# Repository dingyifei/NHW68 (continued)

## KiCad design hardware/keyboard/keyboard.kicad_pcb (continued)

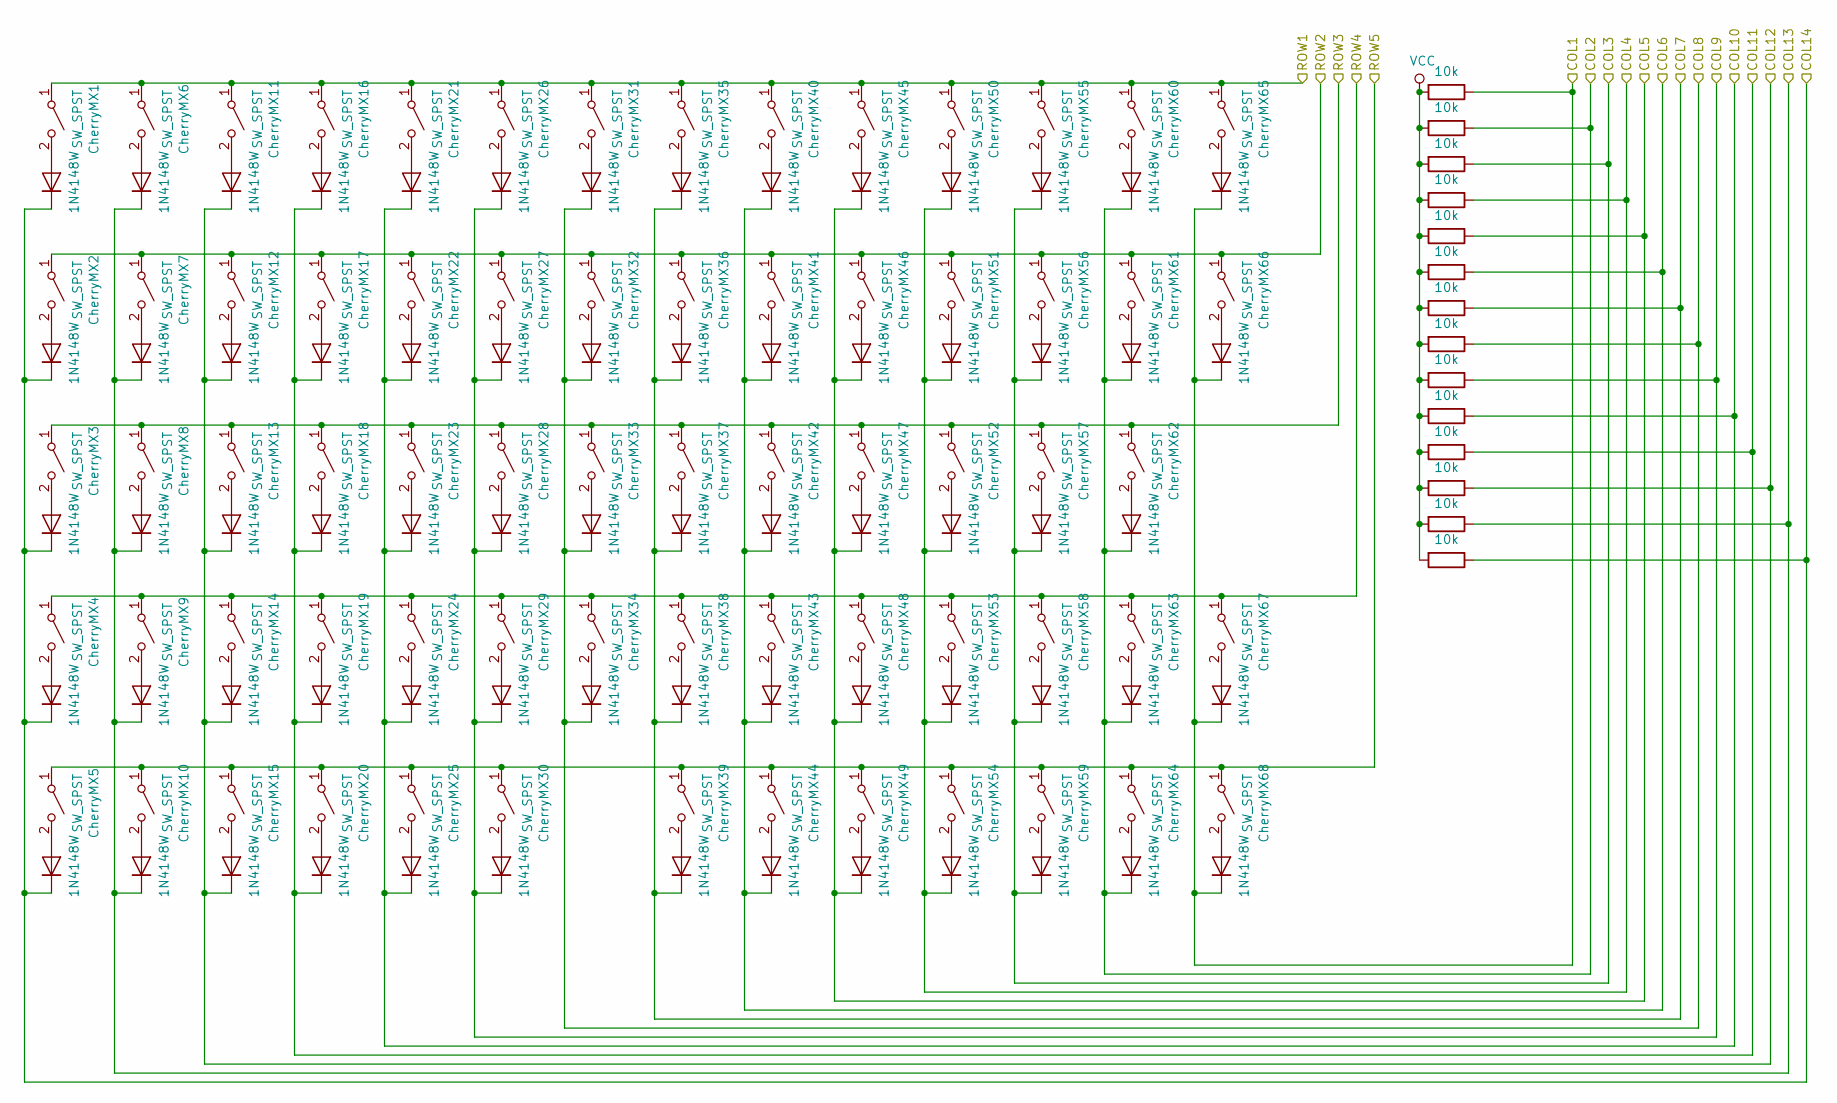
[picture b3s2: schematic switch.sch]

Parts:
CherryMX1, CherryMX2, CherryMX3, CherryMX4, CherryMX5, CherryMX6, CherryMX7, CherryMX8, CherryMX9, CherryMX10, CherryMX11, CherryMX12, CherryMX13, CherryMX14, CherryMX15, CherryMX16, CherryMX17, CherryMX18, CherryMX19, CherryMX20, CherryMX21, CherryMX22, CherryMX23, CherryMX24, CherryMX25, CherryMX26, CherryMX27, CherryMX28, CherryMX29, CherryMX30, CherryMX31, CherryMX32, CherryMX33, CherryMX34, CherryMX35, CherryMX36, CherryMX37, CherryMX38, CherryMX39, CherryMX40, CherryMX41, CherryMX42, CherryMX43, CherryMX44, CherryMX45, CherryMX46, CherryMX47, CherryMX48, CherryMX49, CherryMX50, CherryMX51, CherryMX52, CherryMX53, CherryMX54, CherryMX55, CherryMX56, CherryMX57, CherryMX58, CherryMX59, CherryMX60, CherryMX61, CherryMX62, CherryMX63, CherryMX64, CherryMX65, CherryMX66, CherryMX67, CherryMX68: SW_SPST; Kailh_socket_MX_optional_reversible
D1, D2, D3, D4, D5, D6, D7, D8, D9, D10, D11, D12, D13, D14, D15, D16, D17, D18, D19, D20, D21, D22, D23, D24, D25, D26, D27, D28, D29, D30, D31, D32, D33, D34, D35, D36, D37, D38, D39, D40, D41, D42, D43, D44, D45, D46, D47, D48, D49, D50, D51, D52, D53, D54, D55, D56, D57, D58, D59, D60, D61, D62, D63, D64, D65, D66, D67, D68: 1N4148W; D_SOD-123
R1, R2, R3, R4, R5, R6, R7, R8, R9, R10, R11, R12, R13, R14: 10k; R_0603_1608Metric_Pad1.05x0.95mm_HandSolder

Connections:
/switch/COL1: D65.1 (K), D66.1 (K), D67.1 (K), D68.1 (K), R1.1; also elsewhere on the board
/switch/COL2: D60.1 (K), D61.1 (K), D62.1 (K), D63.1 (K), D64.1 (K), R2.1; also elsewhere on the board
/switch/COL3: D55.1 (K), D56.1 (K), D57.1 (K), D58.1 (K), D59.1 (K), R3.1; also elsewhere on the board
/switch/COL4: D50.1 (K), D51.1 (K), D52.1 (K), D53.1 (K), D54.1 (K), R4.1; also elsewhere on the board
/switch/COL5: D45.1 (K), D46.1 (K), D47.1 (K), D48.1 (K), D49.1 (K), R5.1; also elsewhere on the board
/switch/COL6: D40.1 (K), D41.1 (K), D42.1 (K), D43.1 (K), D44.1 (K), R6.1; also elsewhere on the board
/switch/COL7: D35.1 (K), D36.1 (K), D37.1 (K), D38.1 (K), D39.1 (K), R7.1; also elsewhere on the board
/switch/COL8: D31.1 (K), D32.1 (K), D33.1 (K), D34.1 (K), R8.1; also elsewhere on the board
/switch/COL9: D26.1 (K), D27.1 (K), D28.1 (K), D29.1 (K), D30.1 (K), R9.1; also elsewhere on the board
/switch/COL10: D21.1 (K), D22.1 (K), D23.1 (K), D24.1 (K), D25.1 (K), R10.1; also elsewhere on the board
/switch/COL11: D16.1 (K), D17.1 (K), D18.1 (K), D19.1 (K), D20.1 (K), R11.1; also elsewhere on the board
/switch/COL12: D11.1 (K), D12.1 (K), D13.1 (K), D14.1 (K), D15.1 (K), R12.1; also elsewhere on the board
/switch/COL13: D6.1 (K), D7.1 (K), D8.1 (K), D9.1 (K), D10.1 (K), R13.1; also elsewhere on the board
/switch/COL14: D1.1 (K), D2.1 (K), D3.1 (K), D4.1 (K), D5.1 (K), R14.1; also elsewhere on the board
/switch/ROW1: CherryMX1.1 (A), CherryMX6.1 (A), CherryMX11.1 (A), CherryMX16.1 (A), CherryMX21.1 (A), CherryMX26.1 (A), CherryMX31.1 (A), CherryMX35.1 (A), CherryMX40.1 (A), CherryMX45.1 (A), CherryMX50.1 (A), CherryMX55.1 (A), CherryMX60.1 (A), CherryMX65.1 (A); also elsewhere on the board
/switch/ROW2: CherryMX2.1 (A), CherryMX7.1 (A), CherryMX12.1 (A), CherryMX17.1 (A), CherryMX22.1 (A), CherryMX27.1 (A), CherryMX32.1 (A), CherryMX36.1 (A), CherryMX41.1 (A), CherryMX46.1 (A), CherryMX51.1 (A), CherryMX56.1 (A), CherryMX61.1 (A), CherryMX66.1 (A); also elsewhere on the board
/switch/ROW3: CherryMX3.1 (A), CherryMX8.1 (A), CherryMX13.1 (A), CherryMX18.1 (A), CherryMX23.1 (A), CherryMX28.1 (A), CherryMX33.1 (A), CherryMX37.1 (A), CherryMX42.1 (A), CherryMX47.1 (A), CherryMX52.1 (A), CherryMX57.1 (A), CherryMX62.1 (A); also elsewhere on the board
/switch/ROW4: CherryMX4.1 (A), CherryMX9.1 (A), CherryMX14.1 (A), CherryMX19.1 (A), CherryMX24.1 (A), CherryMX29.1 (A), CherryMX34.1 (A), CherryMX38.1 (A), CherryMX43.1 (A), CherryMX48.1 (A), CherryMX53.1 (A), CherryMX58.1 (A), CherryMX63.1 (A), CherryMX67.1 (A); also elsewhere on the board
/switch/ROW5: CherryMX5.1 (A), CherryMX10.1 (A), CherryMX15.1 (A), CherryMX20.1 (A), CherryMX25.1 (A), CherryMX30.1 (A), CherryMX39.1 (A), CherryMX44.1 (A), CherryMX49.1 (A), CherryMX54.1 (A), CherryMX59.1 (A), CherryMX64.1 (A), CherryMX68.1 (A); also elsewhere on the board
unnamed: CherryMX1.2 (B), D1.2 (A)
unnamed: CherryMX2.2 (B), D2.2 (A)
unnamed: CherryMX3.2 (B), D3.2 (A)
unnamed: CherryMX4.2 (B), D4.2 (A)
unnamed: CherryMX5.2 (B), D5.2 (A)
unnamed: CherryMX6.2 (B), D6.2 (A)
unnamed: CherryMX7.2 (B), D7.2 (A)
unnamed: CherryMX8.2 (B), D8.2 (A)
unnamed: CherryMX9.2 (B), D9.2 (A)
unnamed: CherryMX10.2 (B), D10.2 (A)
unnamed: CherryMX11.2 (B), D11.2 (A)
unnamed: CherryMX12.2 (B), D12.2 (A)
unnamed: CherryMX13.2 (B), D13.2 (A)
unnamed: CherryMX14.2 (B), D14.2 (A)
unnamed: CherryMX15.2 (B), D15.2 (A)
unnamed: CherryMX16.2 (B), D16.2 (A)
unnamed: CherryMX17.2 (B), D17.2 (A)
unnamed: CherryMX18.2 (B), D18.2 (A)
unnamed: CherryMX19.2 (B), D19.2 (A)
unnamed: CherryMX20.2 (B), D20.2 (A)
unnamed: CherryMX21.2 (B), D21.2 (A)
unnamed: CherryMX22.2 (B), D22.2 (A)
unnamed: CherryMX23.2 (B), D23.2 (A)
unnamed: CherryMX24.2 (B), D24.2 (A)
unnamed: CherryMX25.2 (B), D25.2 (A)
unnamed: CherryMX26.2 (B), D26.2 (A)
unnamed: CherryMX27.2 (B), D27.2 (A)
unnamed: CherryMX28.2 (B), D28.2 (A)
unnamed: CherryMX29.2 (B), D29.2 (A)
unnamed: CherryMX30.2 (B), D30.2 (A)
unnamed: CherryMX31.2 (B), D31.2 (A)
unnamed: CherryMX32.2 (B), D32.2 (A)
unnamed: CherryMX33.2 (B), D33.2 (A)
unnamed: CherryMX34.2 (B), D34.2 (A)
unnamed: CherryMX35.2 (B), D35.2 (A)
unnamed: CherryMX36.2 (B), D36.2 (A)
unnamed: CherryMX37.2 (B), D37.2 (A)
unnamed: CherryMX38.2 (B), D38.2 (A)
unnamed: CherryMX39.2 (B), D39.2 (A)
unnamed: CherryMX40.2 (B), D40.2 (A)
unnamed: CherryMX41.2 (B), D41.2 (A)
unnamed: CherryMX42.2 (B), D42.2 (A)
unnamed: CherryMX43.2 (B), D43.2 (A)
unnamed: CherryMX44.2 (B), D44.2 (A)
unnamed: CherryMX45.2 (B), D45.2 (A)
unnamed: CherryMX46.2 (B), D46.2 (A)
unnamed: CherryMX47.2 (B), D47.2 (A)
unnamed: CherryMX48.2 (B), D48.2 (A)
unnamed: CherryMX49.2 (B), D49.2 (A)
unnamed: CherryMX50.2 (B), D50.2 (A)
unnamed: CherryMX51.2 (B), D51.2 (A)
unnamed: CherryMX52.2 (B), D52.2 (A)
unnamed: CherryMX53.2 (B), D53.2 (A)
unnamed: CherryMX54.2 (B), D54.2 (A)
unnamed: CherryMX55.2 (B), D55.2 (A)
unnamed: CherryMX56.2 (B), D56.2 (A)
unnamed: CherryMX57.2 (B), D57.2 (A)
unnamed: CherryMX58.2 (B), D58.2 (A)
unnamed: CherryMX59.2 (B), D59.2 (A)
unnamed: CherryMX60.2 (B), D60.2 (A)
unnamed: CherryMX61.2 (B), D61.2 (A)
unnamed: CherryMX62.2 (B), D62.2 (A)
unnamed: CherryMX63.2 (B), D63.2 (A)
unnamed: CherryMX64.2 (B), D64.2 (A)
unnamed: CherryMX65.2 (B), D65.2 (A)
unnamed: CherryMX66.2 (B), D66.2 (A)
unnamed: CherryMX67.2 (B), D67.2 (A)
unnamed: CherryMX68.2 (B), D68.2 (A)
VCC: R1.2, R2.2, R3.2, R4.2, R5.2, R6.2, R7.2, R8.2, R9.2, R10.2, R11.2, R12.2, R13.2, R14.2; also elsewhere on the board

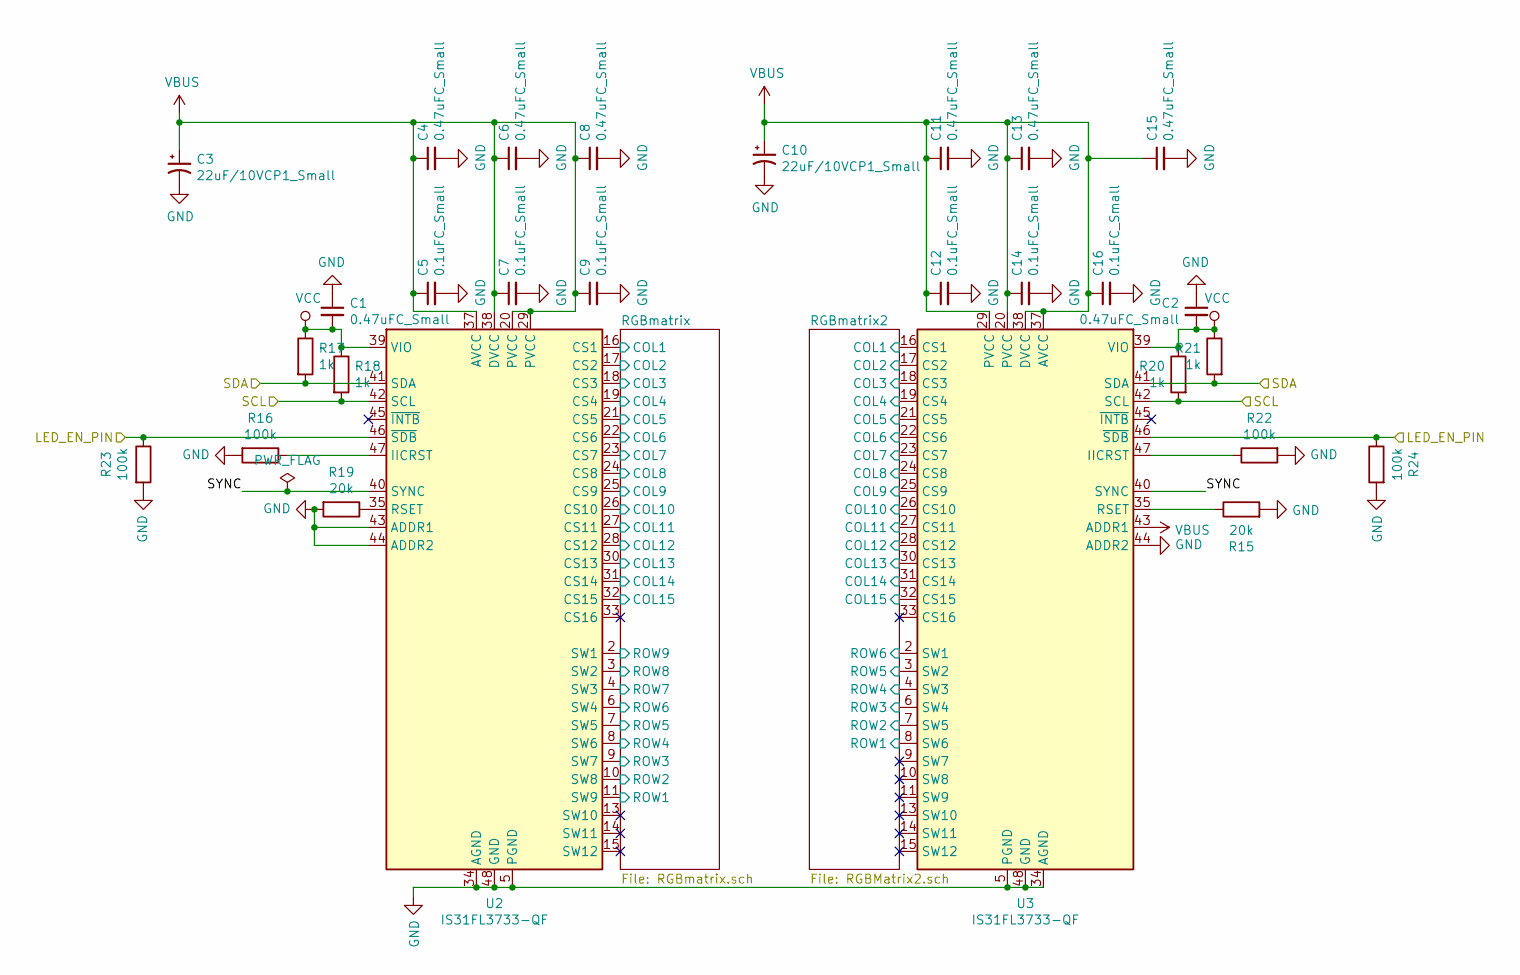
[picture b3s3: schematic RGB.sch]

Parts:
C1, C2, C4, C6, C8, C11, C13, C15: 0.47uFC_Small; C_0603_1608Metric_Pad1.05x0.95mm_HandSolder
C3, C10: 22uF/10VCP1_Small; CP_EIA-3528-12_Kemet-T_Pad1.50x2.35mm_HandSolder
C5, C7, C9, C12, C14, C16: 0.1uFC_Small; C_0603_1608Metric_Pad1.05x0.95mm_HandSolder
R15, R19: 20k; R_0603_1608Metric_Pad1.05x0.95mm_HandSolder
R16, R22, R23, R24: 100k; R_0603_1608Metric_Pad1.05x0.95mm_HandSolder
R17, R18, R20, R21: 1k; R_0603_1608Metric_Pad1.05x0.95mm_HandSolder
U2, U3: IS31FL3733-QF; QFN-48-1EP_6x6mm_P0.4mm_EP4.2x4.2mm_ThermalVias

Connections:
/RGB/LED_EN_PIN: R23.1, R24.1, U2.46 (~SDB), U3.46 (~SDB); also elsewhere on the board
/RGB/RGBmatrix2/COL1: U3.16 (CS1); also elsewhere on the board
/RGB/RGBmatrix2/COL2: U3.17 (CS2); also elsewhere on the board
/RGB/RGBmatrix2/COL3: U3.18 (CS3); also elsewhere on the board
/RGB/RGBmatrix2/COL4: U3.19 (CS4); also elsewhere on the board
/RGB/RGBmatrix2/COL5: U3.21 (CS5); also elsewhere on the board
/RGB/RGBmatrix2/COL6: U3.22 (CS6); also elsewhere on the board
/RGB/RGBmatrix2/COL7: U3.23 (CS7); also elsewhere on the board
/RGB/RGBmatrix2/COL8: U3.24 (CS8); also elsewhere on the board
/RGB/RGBmatrix2/COL9: U3.25 (CS9); also elsewhere on the board
/RGB/RGBmatrix2/COL10: U3.26 (CS10); also elsewhere on the board
/RGB/RGBmatrix2/COL11: U3.27 (CS11); also elsewhere on the board
/RGB/RGBmatrix2/COL12: U3.28 (CS12); also elsewhere on the board
/RGB/RGBmatrix2/COL13: U3.30 (CS13); also elsewhere on the board
/RGB/RGBmatrix2/COL14: U3.31 (CS14); also elsewhere on the board
/RGB/RGBmatrix2/COL15: U3.32 (CS15); also elsewhere on the board
/RGB/RGBmatrix2/ROW1: U3.8 (SW6); also elsewhere on the board
/RGB/RGBmatrix2/ROW2: U3.7 (SW5); also elsewhere on the board
/RGB/RGBmatrix2/ROW3: U3.6 (SW4); also elsewhere on the board
/RGB/RGBmatrix2/ROW4: U3.4 (SW3); also elsewhere on the board
/RGB/RGBmatrix2/ROW5: U3.3 (SW2); also elsewhere on the board
/RGB/RGBmatrix2/ROW6: U3.2 (SW1); also elsewhere on the board
/RGB/RGBmatrix/COL1: U2.16 (CS1); also elsewhere on the board
/RGB/RGBmatrix/COL2: U2.17 (CS2); also elsewhere on the board
/RGB/RGBmatrix/COL3: U2.18 (CS3); also elsewhere on the board
/RGB/RGBmatrix/COL4: U2.19 (CS4); also elsewhere on the board
/RGB/RGBmatrix/COL5: U2.21 (CS5); also elsewhere on the board
/RGB/RGBmatrix/COL6: U2.22 (CS6); also elsewhere on the board
/RGB/RGBmatrix/COL7: U2.23 (CS7); also elsewhere on the board
/RGB/RGBmatrix/COL8: U2.24 (CS8); also elsewhere on the board
/RGB/RGBmatrix/COL9: U2.25 (CS9); also elsewhere on the board
/RGB/RGBmatrix/COL10: U2.26 (CS10); also elsewhere on the board
/RGB/RGBmatrix/COL11: U2.27 (CS11); also elsewhere on the board
/RGB/RGBmatrix/COL12: U2.28 (CS12); also elsewhere on the board
/RGB/RGBmatrix/COL13: U2.30 (CS13); also elsewhere on the board
/RGB/RGBmatrix/COL14: U2.31 (CS14); also elsewhere on the board
/RGB/RGBmatrix/COL15: U2.32 (CS15); also elsewhere on the board
/RGB/RGBmatrix/ROW1: U2.11 (SW9); also elsewhere on the board
/RGB/RGBmatrix/ROW2: U2.10 (SW8); also elsewhere on the board
/RGB/RGBmatrix/ROW3: U2.9 (SW7); also elsewhere on the board
/RGB/RGBmatrix/ROW4: U2.8 (SW6); also elsewhere on the board
/RGB/RGBmatrix/ROW5: U2.7 (SW5); also elsewhere on the board
/RGB/RGBmatrix/ROW6: U2.6 (SW4); also elsewhere on the board
/RGB/RGBmatrix/ROW7: U2.4 (SW3); also elsewhere on the board
/RGB/RGBmatrix/ROW8: U2.3 (SW2); also elsewhere on the board
/RGB/RGBmatrix/ROW9: U2.2 (SW1); also elsewhere on the board
/RGB/SCL: R18.2, R20.2, U2.42 (SCL), U3.42 (SCL); also elsewhere on the board
/RGB/SDA: R17.2, R21.2, U2.41 (SDA), U3.41 (SDA); also elsewhere on the board
/RGB/SYNC: U2.40 (SYNC), U3.40 (SYNC)
GND: C1.1, C2.1, C3.2, C4.2, C5.2, C6.2, C7.2, C8.2, C9.2, C10.2, C11.2, C12.2, C13.2, C14.2, C15.2, C16.2, R15.2, R16.2, R19.2, R22.2, R23.2, R24.2, U2.5 (PGND), U2.12 (PGND), U2.34 (AGND), U2.43 (ADDR1), U2.44 (ADDR2), U2.48 (GND), U2.49 (GND), U3.5 (PGND), U3.12 (PGND), U3.34 (AGND), U3.44 (ADDR2), U3.48 (GND), U3.49 (GND); also elsewhere on the board
unnamed: R15.1, U3.35 (RSET)
unnamed: R16.1, U2.47 (IICRST)
unnamed: R19.1, U2.35 (RSET)
unnamed: R22.1, U3.47 (IICRST)
VBUS: C3.1, C4.1, C5.1, C6.1, C7.1, C8.1, C9.1, C10.1, C11.1, C12.1, C13.1, C14.1, C15.1, C16.1, U2.20 (PVCC), U2.29 (PVCC), U2.37 (AVCC), U2.38 (DVCC), U3.20 (PVCC), U3.29 (PVCC), U3.37 (AVCC), U3.38 (DVCC), U3.43 (ADDR1); also elsewhere on the board
VCC: C1.2, C2.2, R17.1, R18.1, R20.1, R21.1, U2.39 (VIO), U3.39 (VIO); also elsewhere on the board

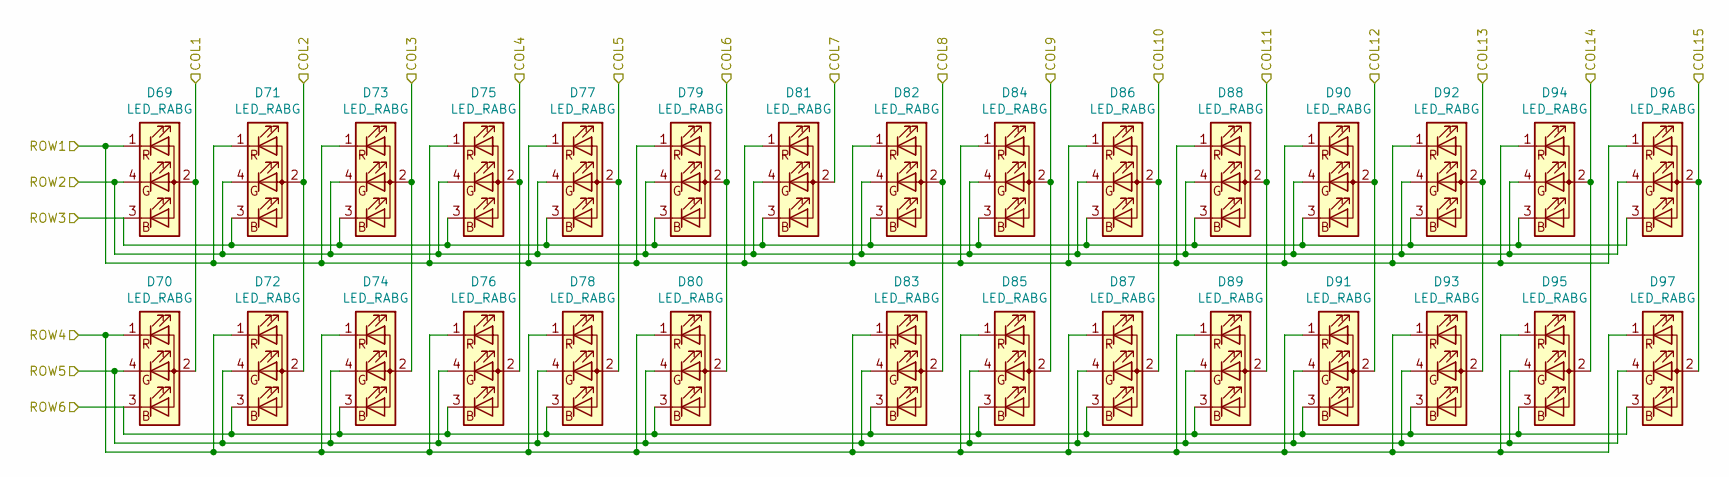
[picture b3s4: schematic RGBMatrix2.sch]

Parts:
D69, D70, D71, D72, D73, D74, D75, D76, D77, D78, D79, D80, D81, D82, D83, D84, D85, D86, D87, D88, D89, D90, D91, D92, D93, D94, D95, D96, D97: LED_RABG

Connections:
/RGB/RGBmatrix2/COL1: D69.2 (A), D70.2 (A); also elsewhere on the board
/RGB/RGBmatrix2/COL2: D71.2 (A), D72.2 (A); also elsewhere on the board
/RGB/RGBmatrix2/COL3: D73.2 (A), D74.2 (A); also elsewhere on the board
/RGB/RGBmatrix2/COL4: D75.2 (A), D76.2 (A); also elsewhere on the board
/RGB/RGBmatrix2/COL5: D77.2 (A), D78.2 (A); also elsewhere on the board
/RGB/RGBmatrix2/COL6: D79.2 (A), D80.2 (A); also elsewhere on the board
/RGB/RGBmatrix2/COL7: D81.2 (A); also elsewhere on the board
/RGB/RGBmatrix2/COL8: D82.2 (A), D83.2 (A); also elsewhere on the board
/RGB/RGBmatrix2/COL9: D84.2 (A), D85.2 (A); also elsewhere on the board
/RGB/RGBmatrix2/COL10: D86.2 (A), D87.2 (A); also elsewhere on the board
/RGB/RGBmatrix2/COL11: D88.2 (A), D89.2 (A); also elsewhere on the board
/RGB/RGBmatrix2/COL12: D90.2 (A), D91.2 (A); also elsewhere on the board
/RGB/RGBmatrix2/COL13: D92.2 (A), D93.2 (A); also elsewhere on the board
/RGB/RGBmatrix2/COL14: D94.2 (A), D95.2 (A); also elsewhere on the board
/RGB/RGBmatrix2/COL15: D96.2 (A), D97.2 (A); also elsewhere on the board
/RGB/RGBmatrix2/ROW1: D69.1 (RK), D71.1 (RK), D73.1 (RK), D75.1 (RK), D77.1 (RK), D79.1 (RK), D81.1 (RK), D82.1 (RK), D84.1 (RK), D86.1 (RK), D88.1 (RK), D90.1 (RK), D92.1 (RK), D94.1 (RK), D96.1 (RK); also elsewhere on the board
/RGB/RGBmatrix2/ROW2: D69.4 (GK), D71.4 (GK), D73.4 (GK), D75.4 (GK), D77.4 (GK), D79.4 (GK), D81.4 (GK), D82.4 (GK), D84.4 (GK), D86.4 (GK), D88.4 (GK), D90.4 (GK), D92.4 (GK), D94.4 (GK), D96.4 (GK); also elsewhere on the board
/RGB/RGBmatrix2/ROW3: D69.3 (BK), D71.3 (BK), D73.3 (BK), D75.3 (BK), D77.3 (BK), D79.3 (BK), D81.3 (BK), D82.3 (BK), D84.3 (BK), D86.3 (BK), D88.3 (BK), D90.3 (BK), D92.3 (BK), D94.3 (BK), D96.3 (BK); also elsewhere on the board
/RGB/RGBmatrix2/ROW4: D70.1 (RK), D72.1 (RK), D74.1 (RK), D76.1 (RK), D78.1 (RK), D80.1 (RK), D83.1 (RK), D85.1 (RK), D87.1 (RK), D89.1 (RK), D91.1 (RK), D93.1 (RK), D95.1 (RK), D97.1 (RK); also elsewhere on the board
/RGB/RGBmatrix2/ROW5: D70.4 (GK), D72.4 (GK), D74.4 (GK), D76.4 (GK), D78.4 (GK), D80.4 (GK), D83.4 (GK), D85.4 (GK), D87.4 (GK), D89.4 (GK), D91.4 (GK), D93.4 (GK), D95.4 (GK), D97.4 (GK); also elsewhere on the board
/RGB/RGBmatrix2/ROW6: D70.3 (BK), D72.3 (BK), D74.3 (BK), D76.3 (BK), D78.3 (BK), D80.3 (BK), D83.3 (BK), D85.3 (BK), D87.3 (BK), D89.3 (BK), D91.3 (BK), D93.3 (BK), D95.3 (BK), D97.3 (BK); also elsewhere on the board

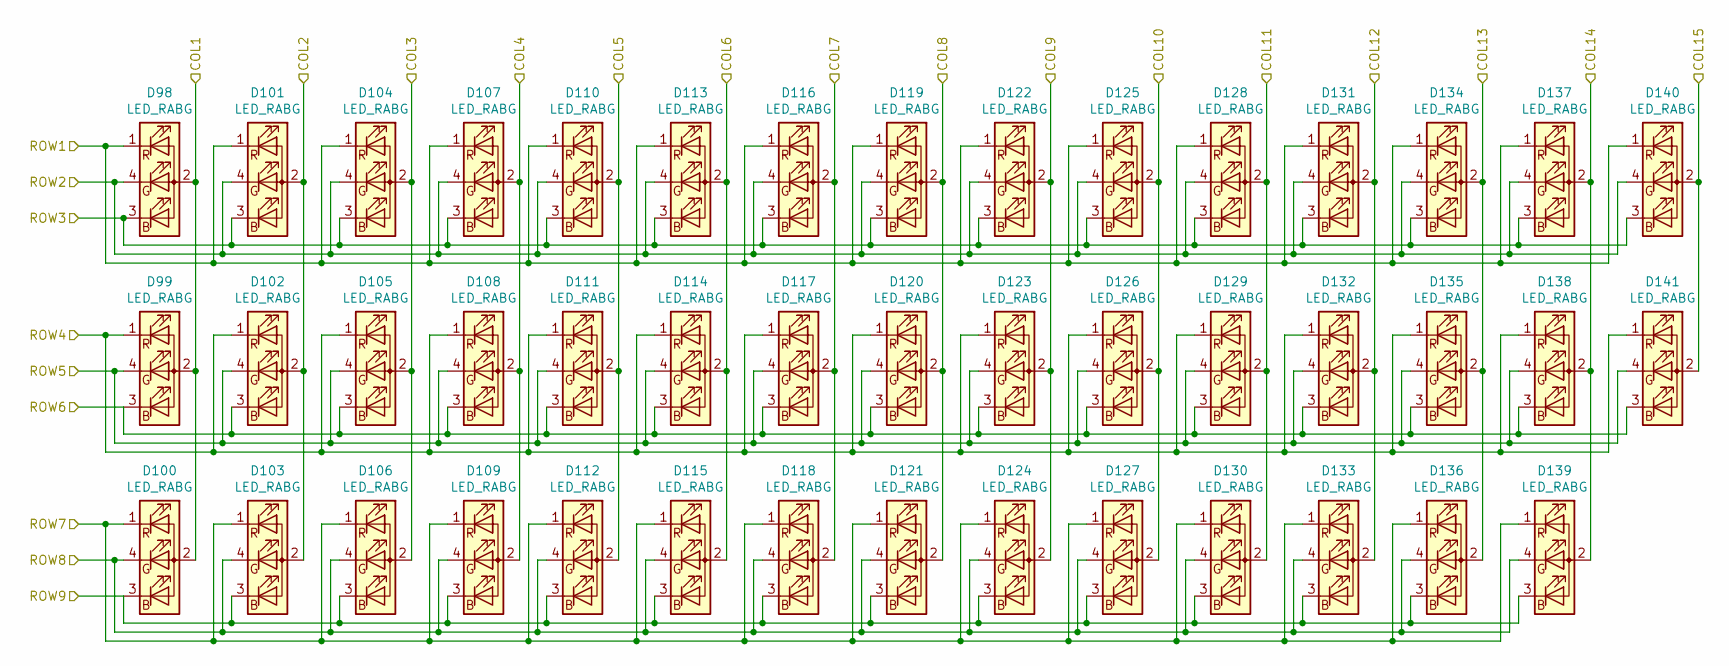
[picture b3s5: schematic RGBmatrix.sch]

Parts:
D98, D99, D100, D101, D102, D103, D104, D105, D106, D107, D108, D109, D110, D111, D112, D113, D114, D115, D116, D117, D118, D119, D120, D121, D122, D123, D124, D125, D126, D127, D128, D129, D130, D131, D132, D133, D134, D135, D136, D137, D138, D139, D140, D141: LED_RABG

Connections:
/RGB/RGBmatrix/COL1: D98.2 (A), D99.2 (A), D100.2 (A); also elsewhere on the board
/RGB/RGBmatrix/COL2: D101.2 (A), D102.2 (A), D103.2 (A); also elsewhere on the board
/RGB/RGBmatrix/COL3: D104.2 (A), D105.2 (A), D106.2 (A); also elsewhere on the board
/RGB/RGBmatrix/COL4: D107.2 (A), D108.2 (A), D109.2 (A); also elsewhere on the board
/RGB/RGBmatrix/COL5: D110.2 (A), D111.2 (A), D112.2 (A); also elsewhere on the board
/RGB/RGBmatrix/COL6: D113.2 (A), D114.2 (A), D115.2 (A); also elsewhere on the board
/RGB/RGBmatrix/COL7: D116.2 (A), D117.2 (A), D118.2 (A); also elsewhere on the board
/RGB/RGBmatrix/COL8: D119.2 (A), D120.2 (A), D121.2 (A); also elsewhere on the board
/RGB/RGBmatrix/COL9: D122.2 (A), D123.2 (A), D124.2 (A); also elsewhere on the board
/RGB/RGBmatrix/COL10: D125.2 (A), D126.2 (A), D127.2 (A); also elsewhere on the board
/RGB/RGBmatrix/COL11: D128.2 (A), D129.2 (A), D130.2 (A); also elsewhere on the board
/RGB/RGBmatrix/COL12: D131.2 (A), D132.2 (A), D133.2 (A); also elsewhere on the board
/RGB/RGBmatrix/COL13: D134.2 (A), D135.2 (A), D136.2 (A); also elsewhere on the board
/RGB/RGBmatrix/COL14: D137.2 (A), D138.2 (A), D139.2 (A); also elsewhere on the board
/RGB/RGBmatrix/COL15: D140.2 (A), D141.2 (A); also elsewhere on the board
/RGB/RGBmatrix/ROW1: D98.1 (RK), D101.1 (RK), D104.1 (RK), D107.1 (RK), D110.1 (RK), D113.1 (RK), D116.1 (RK), D119.1 (RK), D122.1 (RK), D125.1 (RK), D128.1 (RK), D131.1 (RK), D134.1 (RK), D137.1 (RK), D140.1 (RK); also elsewhere on the board
/RGB/RGBmatrix/ROW2: D98.4 (GK), D101.4 (GK), D104.4 (GK), D107.4 (GK), D110.4 (GK), D113.4 (GK), D116.4 (GK), D119.4 (GK), D122.4 (GK), D125.4 (GK), D128.4 (GK), D131.4 (GK), D134.4 (GK), D137.4 (GK), D140.4 (GK); also elsewhere on the board
/RGB/RGBmatrix/ROW3: D98.3 (BK), D101.3 (BK), D104.3 (BK), D107.3 (BK), D110.3 (BK), D113.3 (BK), D116.3 (BK), D119.3 (BK), D122.3 (BK), D125.3 (BK), D128.3 (BK), D131.3 (BK), D134.3 (BK), D137.3 (BK), D140.3 (BK); also elsewhere on the board
/RGB/RGBmatrix/ROW4: D99.1 (RK), D102.1 (RK), D105.1 (RK), D108.1 (RK), D111.1 (RK), D114.1 (RK), D117.1 (RK), D120.1 (RK), D123.1 (RK), D126.1 (RK), D129.1 (RK), D132.1 (RK), D135.1 (RK), D138.1 (RK), D141.1 (RK); also elsewhere on the board
/RGB/RGBmatrix/ROW5: D99.4 (GK), D102.4 (GK), D105.4 (GK), D108.4 (GK), D111.4 (GK), D114.4 (GK), D117.4 (GK), D120.4 (GK), D123.4 (GK), D126.4 (GK), D129.4 (GK), D132.4 (GK), D135.4 (GK), D138.4 (GK), D141.4 (GK); also elsewhere on the board
/RGB/RGBmatrix/ROW6: D99.3 (BK), D102.3 (BK), D105.3 (BK), D108.3 (BK), D111.3 (BK), D114.3 (BK), D117.3 (BK), D120.3 (BK), D123.3 (BK), D126.3 (BK), D129.3 (BK), D132.3 (BK), D135.3 (BK), D138.3 (BK), D141.3 (BK); also elsewhere on the board
/RGB/RGBmatrix/ROW7: D100.1 (RK), D103.1 (RK), D106.1 (RK), D109.1 (RK), D112.1 (RK), D115.1 (RK), D118.1 (RK), D121.1 (RK), D124.1 (RK), D127.1 (RK), D130.1 (RK), D133.1 (RK), D136.1 (RK), D139.1 (RK); also elsewhere on the board
/RGB/RGBmatrix/ROW8: D100.4 (GK), D103.4 (GK), D106.4 (GK), D109.4 (GK), D112.4 (GK), D115.4 (GK), D118.4 (GK), D121.4 (GK), D124.4 (GK), D127.4 (GK), D130.4 (GK), D133.4 (GK), D136.4 (GK), D139.4 (GK); also elsewhere on the board
/RGB/RGBmatrix/ROW9: D100.3 (BK), D103.3 (BK), D106.3 (BK), D109.3 (BK), D112.3 (BK), D115.3 (BK), D118.3 (BK), D121.3 (BK), D124.3 (BK), D127.3 (BK), D130.3 (BK), D133.3 (BK), D136.3 (BK), D139.3 (BK); also elsewhere on the board

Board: 2 copper layers, 252 parts (0 on the bottom side), 143 nets, no tracks yet.

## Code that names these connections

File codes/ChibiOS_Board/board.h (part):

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/*
 * GPIOA setup:
 *
 * PA0  - BUTTON                    (input floating).
 * PA1  - PIN1                      (input pullup).
 * PA2  - PIN2                      (input pullup).
 * PA3  - PIN3                      (input pullup).
 * PA4  - PIN4                      (input pullup).
 * PA5  - SPI1_SCK L3GD20_SCL       (alternate 5).
 * PA6  - SPI1_MISO L3GD20_SDO      (alternate 5).
 * PA7  - SPI1_MOSI L3GD20_SDI      (alternate 5).
 * PA8  - PIN8                      (input pullup).
 * PA9  - PIN9                      (input pullup).
 * PA10 - PIN10                     (input pullup).
 * PA11 - USB_DM                    (alternate 14).
 * PA12 - USB_DP                    (alternate 14).
 * PA13 - SWDIO                     (alternate 0).
 * PA14 - SWCLK                     (alternate 0).
 * PA15 - PIN15                     (input pullup).
 */
#define VAL_GPIOA_MODER             (PIN_MODE_INPUT(GPIOA_BUTTON) |         \
                                     PIN_MODE_INPUT(GPIOA_PIN1) |           \
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/*
 * GPIOB setup:
 *
 * PB0  - PIN0                      (input pullup).
 * PB1  - PIN1                      (input pullup).
 * PB2  - PIN2                      (input pullup).
 * PB3  - SWO                       (alternate 0).
 * PB4  - PIN4                      (input pullup).
 * PB5  - PIN5                      (input pullup).
 * PB6  - I2C1_SCL LSM303DLHC_SCL   (alternate 4).
 * PB7  - I2C1_SDA LSM303DLHC_SDA   (alternate 4).
 * PB8  - PIN8                      (input pullup).
 * PB9  - PIN9                      (input pullup).
 * PB10 - PIN10                     (input pullup).
 * PB11 - PIN11                     (input pullup).
 * PB12 - PIN12                     (input pullup).
 * PB13 - PIN13                     (input pullup).
 * PB14 - PIN14                     (input pullup).
 * PB15 - PIN15                     (input pullup).
 */
#define VAL_GPIOB_MODER             (PIN_MODE_INPUT(GPIOB_PIN0) |           \
                                     PIN_MODE_INPUT(GPIOB_PIN1) |           \
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 * PC1  - PIN1                      (input pullup).
 * PC2  - PIN2                      (input pullup).
 * PC3  - PIN3                      (input pullup).
 * PC4  - VCP_RX                    (alternate 7).
 * PC5  - VCP_TX                    (alternate 7).
 * PC6  - PIN6                      (input pullup).
 * PC7  - PIN7                      (input pullup).
 * PC8  - PIN8                      (input pullup).
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/*
 * GPIOF setup:
 *
 * PF0  - OSC_IN                    (input floating).
 * PF1  - OSC_OUT                   (input floating).
 * PF2  - PIN2                      (input pullup).
 * PF3  - PIN3                      (input pullup).
 * PF4  - PIN4                      (input pullup).
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
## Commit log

2019-12-29 At least I'm working on it....
2019-12-31 I think im connecting the pins correctly on RGB...
2020-01-01 switch to proper type of RGB(Common anode)
2020-01-01 Use proper capacitors
2020-01-01 fix unconnected rgb
2020-01-01 now it should be using the correct rgb symbol (RABG)
2020-01-01 use proper footprint, link symbols and footprints
2020-01-01 make everything cleaner
2020-01-01 finally the net is kinda working
2020-01-03 outline done
2020-01-04 Line up most parts and fix some problems with the part
    1.Fix the LED footprint size
    2.Edit the hotplug to be simpler (removed 2 holes)
    3.Line up everything and the silkscreen
    4. Fix the LED matrix and the switch matrix sch
2020-01-06 I think I figured it out
2020-01-06 The keys are finally connected
2020-01-07 Make it better by get rid of the protonC
    1. Remove protonC. use STM32F303CCT6 instead
    2.Use parts based on avalibility
    3.Extend the case so it now fits more parts( should be big enough
    4. A reasonable USB connector
    5. Probably a working DC-DC solution to providde 3.3V
    6. Move 3733's 5V to only 3.3V (maybe it won't work?)
2020-01-07 I think I don't need those pull ups, if i really need it, add them later
2020-01-10 clear all the traces
2020-01-11 PSU placed
2020-01-12 PCB is done??
2020-01-12 Update readme.md
    add the 3d model link
2020-01-12 mistake happens
2020-01-12 fix pictures
2020-01-13 starting the testing PCB
2020-01-13 remove useless files
2020-01-16 making testing PCB, making sure the DFU mode is correct
2020-01-18 Full Send, SMT assembly LOL
2020-01-18 small changes
2020-01-23 Making progress, so many distance warning!!!
2020-01-24 Rotate the RGB controller. gonna have a lot of work to do
2020-01-25 getting closer to it actually works
2020-01-25 Use the correct Footprint
    I think I can't do more things before the parts arrive and figure out what LED im going to use
2020-01-25 add in everything I need
2020-01-25 Initialization
2020-01-26 Im not sure I really need this board config thing
2020-01-28 creating the info.json and starting my configuration journey
2020-01-28 alot of changes
    modify the QFN-48 so PCB 3d view in future would look better (so I don't design a part that doesn't fit)
    I made a useless QFN-40 3d model
    modify schematics so it looks better
2020-01-29 Clear the errors
2020-01-29 Connecting RGBs
2020-01-29 I guess it is done, maybe just make it?
2020-01-30 making progress
2020-01-31 Wiring now have no errors and uses less vias
2020-02-01 minor changes to the LED controller PCB layout, make it much better
2020-02-01 Make it nicer, rev0.1 alpha
2020-02-01 AHHH I can't count, also rename to remove some bugs
2020-02-01 attempt to remove some extra values
2020-02-01 Now it should be working just fine
2020-02-01 add in part number so I could use it for the bom
2020-02-02 update render, remove useless files, fix the decoupeling
2020-02-02 minor changes
2020-02-03 Move the Crystal and made a keepout ring
2020-02-03 small improvements (cap distance)
2020-02-03 vias, don't know why but people put them.... so i put them there just in case
2020-02-04 fix major issues about the I2C pull up, add in debug
2020-02-04 can't do only one commit right?
2020-02-04 always find small things after a commit
2020-02-05 Make sure GPL done correctly, rev0.2 ready, not going to make it either
    Need to make it nicer
2020-02-05 I never remember to fix silkscreen...
2020-02-05 I have fish memory
2020-02-05 I don't know why but i can't count
2020-02-05 forgot to change the picture
2020-02-05 Testing is going to be a seperate project
2020-02-06 changed something
2020-02-07 changed to 0603
2020-02-09 Rev 0.5
    1. Use a better 1205 LED (much chaper on LCSC)
    2. Fix the crystal CL, Rext
    3. did a better job on wiring (but might come with power issues?)
    4. fix the key position (0.01mm shifted so its a big fix)
    5. generate better bom files
    6. add in LCSC and part number so easier to source
2020-02-09 rev 0.5 fixed
2020-02-11 0.6 I hate these auto generated code from STM32Cube
    1. ready for the firmware nightmare
    2. adjust the M3 screw holes
    3. add tooling holes for future PCBA
    4. if nothing go wrong, this will be the V1 after testing
2020-02-11 fix some minor detail, I guess its v0.7
2020-02-13 Remove some unused
2020-02-13 It is the last update of 1206 RGB design, going to switch LED again, correct the 1206 name
2020-02-15 I might just have to stick with 1206/4 did some research, maybe time to make another minimal system board....
2020-02-15 fixing the Tantalum
2020-02-16 Code kinda works
2020-02-16 Now it could compile
2020-02-16 add a script to generate release files
2020-02-17 Fix the button I can't buy... Change part selections for avalibiliby issues
2020-02-18 somehow things aren't working, have to figrue it out
2020-02-18 adding some magics
2020-02-20 going to make it (prototype!)
2020-02-21 Appearently buy parts is hard
2020-03-08 adjust the pcb
2020-03-08 make pads looks better
2020-03-17 small adjustments
2020-03-30 fix some code, trying to figure out the plate
2020-04-04 change footprint
2020-04-04 adjust edge cut
2020-04-05 Cleanup, make everything nice, get ready for making it on JLC
2020-04-05 fix links (It shows I'm a windows peasant lmao)
2020-04-05 adjust layout a tiny bit, make everything nicer
    It's time for V1.0, just double check beffore I sent it to fab
2020-04-05 sometimes the markdown just isn't happy to function
2020-04-05 change stuff so everything export the right way
2020-04-05 fix the cost estimate
2020-04-06 fix some detail for 1.0
2020-04-06 v1.1, too many problems I have to fix
2020-04-18 v2 in progress, update readme
2020-06-01 make things nicer
2020-08-26 project clean up
2020-08-26 Board clean up
2020-08-28 Non-RGB
2020-10-19 Update issue templates
